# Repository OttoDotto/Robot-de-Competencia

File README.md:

# Proyecto Robot de Competencia

Este repositorio contiene el diseño y desarrollo de un **robot móvil autónomo** basado en **ESP32**, pensado para competencias de **seguidores de línea** y adaptable a otras categorías (sumo o fútbol robótico).

## 🏁 Objetivo
Este proyecto representa el **primer paso de la Facultad del Ejército Argentino en el mundo de la robótica competitiva**.  
Más allá del desarrollo técnico, nuestro propósito es:  
- Introducirnos en el ámbito de las competencias robóticas estudiantiles.  
- Presentar a nuestra institución en la comunidad tecnológica.  
- Generar experiencia para futuras participaciones en categorías como seguidor de línea, fútbol robótico y sumo.  
- Sentar las bases para que, en el futuro, la Facultad pueda convertirse en **sede de competencias de robótica**.  

## 🔧 Características principales
- **Microcontrolador**: ESP32 DevKit V1
- **Motores**: 2 × DC Pololu con controladores DRV8833 en configuración paralela
- **Sensores**: Array de 8 sensores reflectivos (QTR-8A)
- **Estructura**: Base y Diseño fabricado en impresión 3D
- **Conectividad**: Bluetooth, Wi-Fi y Control con mando PS
- **Aplicaciones**:  
  - Seguidor de línea (principal)  
  - Adaptación a fútbol robótico

## 📂 Contenido del repositorio
- `/Pcb Kicad` → esquemáticos y PCB en KiCad
- `/Fabricacion` → archivos para fabricacion casera del PCB
- `/Programacion` → códigos utilizados (Motores, Sensores, etc.)
- `/Documentos` → documentación, datasheets, imágenes de referencia del proyecto
- `/Galeria` → Fotografias, videos e imagenes del proyecto

## 📸 Galería (soon tm)

## 👥 Autores
Proyecto desarrollado en la **Facultad del Ejército Argentino** por el equipo **Legión de Ohm**.

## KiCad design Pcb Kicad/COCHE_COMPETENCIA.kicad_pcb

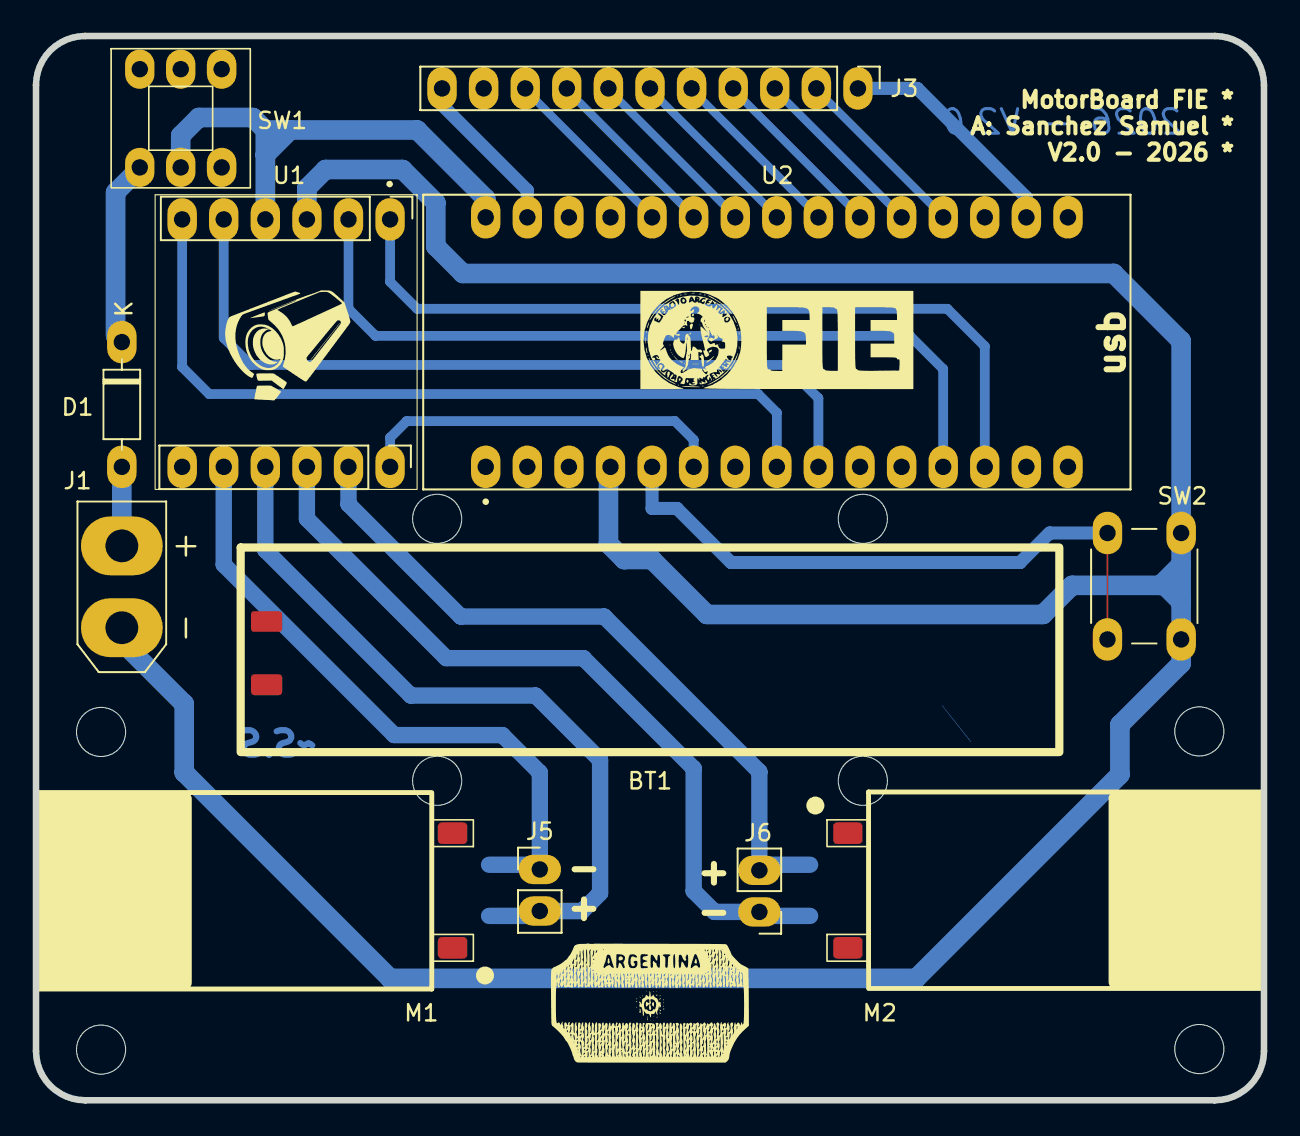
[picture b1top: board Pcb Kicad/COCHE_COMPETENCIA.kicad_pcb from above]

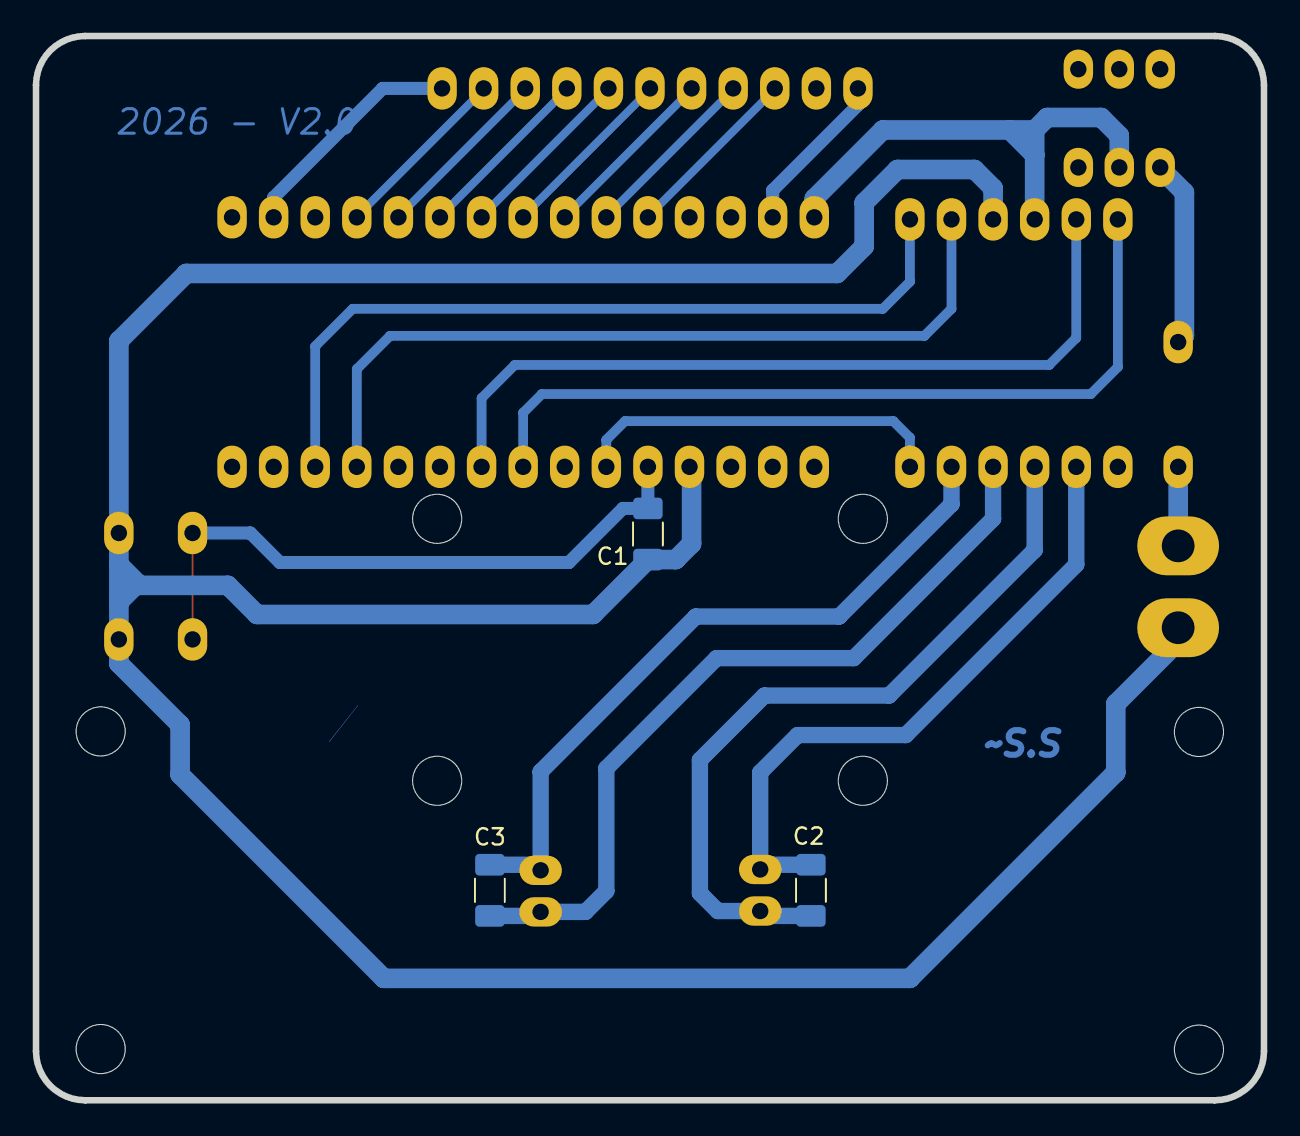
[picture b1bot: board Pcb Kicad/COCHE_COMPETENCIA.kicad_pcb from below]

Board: 2 copper layers, 75.0 x 65.0 mm, 15 parts (3 on the bottom side), 24 nets.

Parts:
BT1: 2S 70C 250mAH; Bateria_Lado
C1, C2, C3: 100n; C_1206_3216Metric_Pad1.33x1.80mm_HandSolder
D1: D_Schottky; D_DO-35_SOD27_P7.62mm_Horizontal
J1: BAT; AMASS_XT30UPB-M_1x02_P5.0mm_Vertical
J3: SENSORES; PinHeader_1x11_P2.54mm_Vertical
J5: M1; PinHeader_1x02_P2.54mm_Vertical
J6: M2; PinHeader_1x02_P2.54mm_Vertical
M1, M2: Pololu DC; pololu
SW1: ON/OFF; SWITCH_6PINS
SW2: SW_RUN; SW_PUSH_6mm_H5mm
U1: DRV8833
U2: ARDUINO_NANO; MODULE_ARDUINO_NANO

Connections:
+3.3V: J3.1, U2.17 (3V3)
/BAT+: D1.2 (A), J1.2
/IN_M1_A: U1.1 (IN4), U2.13 (D10)
/IN_M1_B: U1.2 (IN3), U2.12 (D9)
/IN_M2_A: U1.5 (IN2), U2.9 (D6)
/IN_M2_B: U1.6 (IN1), U2.8 (D5)
/OUT1+: C2.2, J5.2, U1.9 (OUT3)
/OUT1-: C2.1, J5.1, U1.8 (OUT4)
/OUT2+: C3.1, J6.2, U1.11 (OUT1)
/OUT2-: C3.2, J6.1, U1.10 (OUT2)
/S1: J3.9, U2.26 (A7)
/S2: J3.8, U2.25 (A6)
/S3: J3.7, U2.24 (A5)
/S4: J3.6, U2.23 (A4)
/S5: J3.5, U2.22 (A3)
/S6: J3.4, U2.21 (A2)
/S7: J3.3, U2.20 (A1)
/S8: J3.2, U2.19 (A0)
/SLEEP: U1.12 (SLEEP), U2.6 (D3)
/SW1: C1.1, SW2.1, U2.5 (D2)
GND: J3.11, U2.29 (GND_29)
GND_BAT: C1.2, J1.1, SW2.2, U1.3 (GND), U2.4 (GND_4)
unnamed: D1.1 (K), SW1.3 (B)
VCC: SW1.2 (C), U1.4 (VCC), U2.30 (VIN)

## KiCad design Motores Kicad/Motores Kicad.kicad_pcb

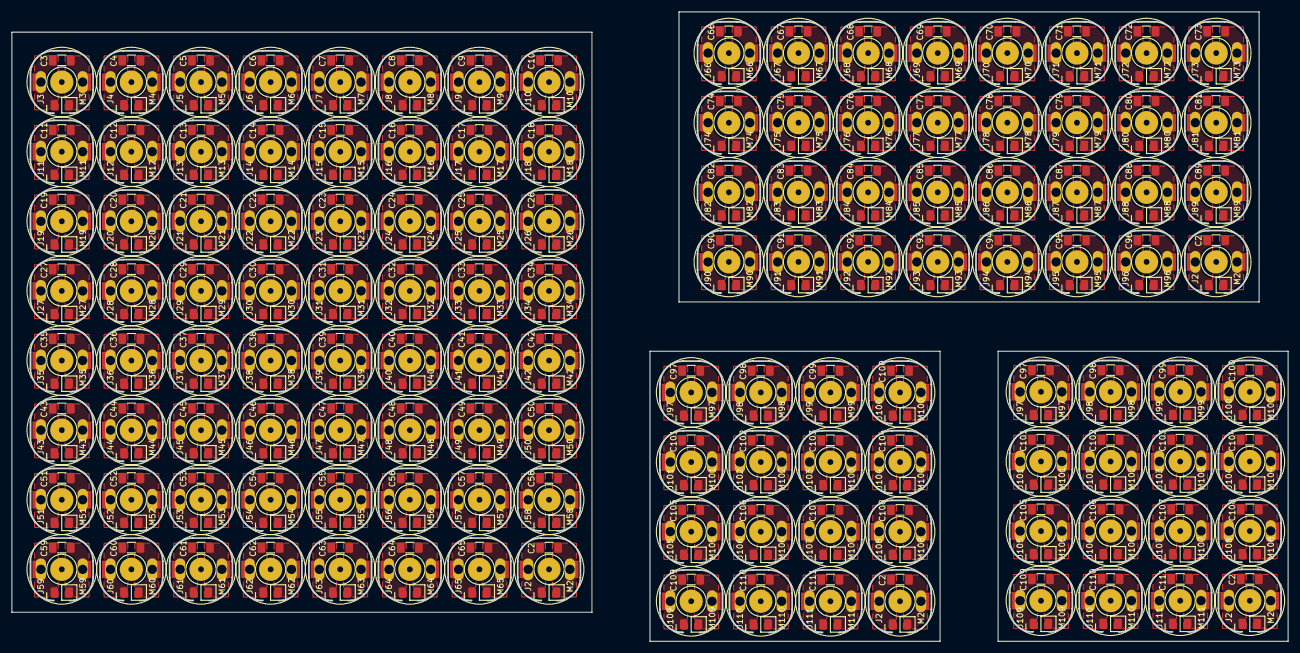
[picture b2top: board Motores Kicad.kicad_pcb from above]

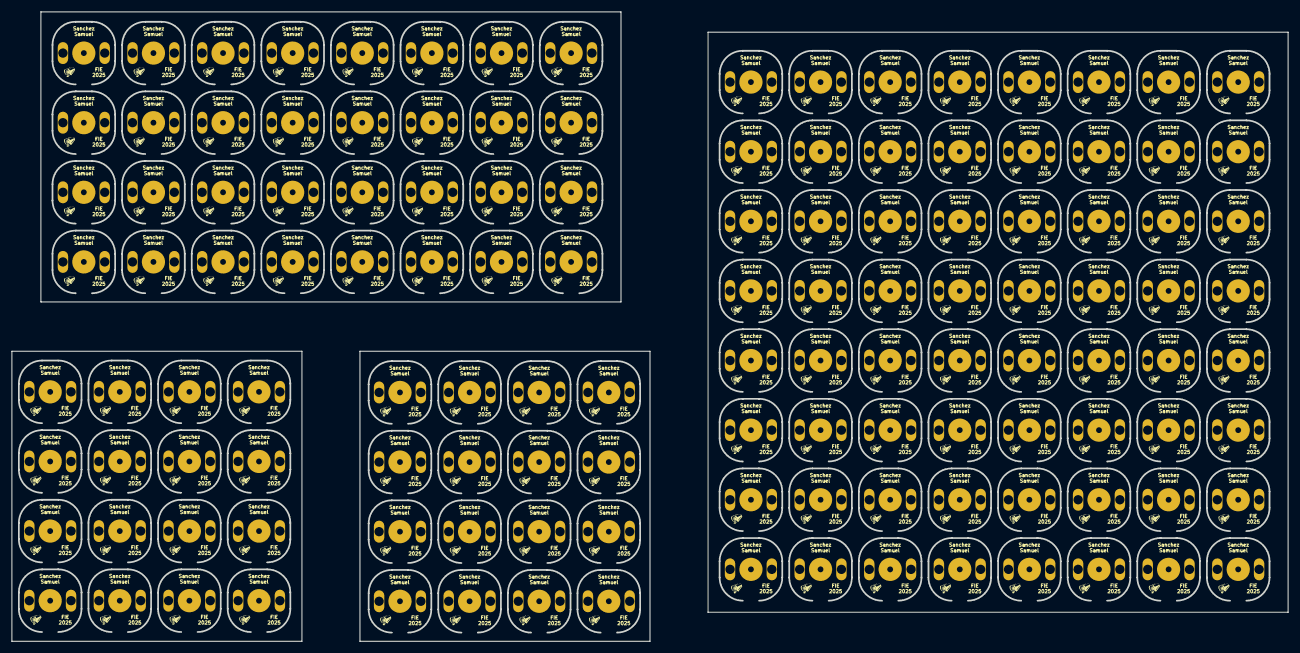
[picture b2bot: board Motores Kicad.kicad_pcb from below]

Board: 2 copper layers, 220.0 x 108.5 mm, 512 parts (128 on the bottom side), 2 nets, no tracks yet.

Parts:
C2, C2#2, C2#3, C2#4, C3, C4, C5, C6, C7, C8, C9, C10, C11, C12, C13, C14, C15, C16, C17, C18, C19, C20, C21, C22, C23, C24, C25, C26, C27, C28, C29, C30, C31, C32, C33, C34, C35, C36, C37, C38, C39, C40, C41, C42, C43, C44, C45, C46, C47, C48, C49, C50, C51, C52, C53, C54, C55, C56, C57, C58, C59, C60, C61, C62, C63, C64, C65, C66, C67, C68, C69, C70, C71, C72, C73, C74, C75, C76, C77, C78, C79, C80, C81, C82, C83, C84, C85, C86, C87, C88, C89, C90, C91, C92, C93, C94, C95, C96, C97, C97#2, C98, C98#2, C99, C99#2, C100, C100#2, C101, C101#2, C102, C102#2, C103, C103#2, C104, C104#2, C105, C105#2, C106, C106#2, C107, C107#2, C108, C108#2, C109, C109#2, C110, C110#2, C111, C111#2: 3.3nF; C_1206_3216Metric_Pad1.33x1.80mm_HandSolder
J2, J2#2, J2#3, J2#4, J3, J4, J5, J6, J7, J8, J9, J10, J11, J12, J13, J14, J15, J16, J17, J18, J19, J20, J21, J22, J23, J24, J25, J26, J27, J28, J29, J30, J31, J32, J33, J34, J35, J36, J37, J38, J39, J40, J41, J42, J43, J44, J45, J46, J47, J48, J49, J50, J51, J52, J53, J54, J55, J56, J57, J58, J59, J60, J61, J62, J63, J64, J65, J66, J67, J68, J69, J70, J71, J72, J73, J74, J75, J76, J77, J78, J79, J80, J81, J82, J83, J84, J85, J86, J87, J88, J89, J90, J91, J92, J93, J94, J95, J96, J97, J97#2, J98, J98#2, J99, J99#2, J100, J100#2, J101, J101#2, J102, J102#2, J103, J103#2, J104, J104#2, J105, J105#2, J106, J106#2, J107, J107#2, J108, J108#2, J109, J109#2, J110, J110#2, J111, J111#2: Vertical; PinHeader_1x02_P2.54mm_Vertical
M2, M2#2, M2#3, M2#4, M3, M4, M5, M6, M7, M8, M9, M10, M11, M12, M13, M14, M15, M16, M17, M18, M19, M20, M21, M22, M23, M24, M25, M26, M27, M28, M29, M30, M31, M32, M33, M34, M35, M36, M37, M38, M39, M40, M41, M42, M43, M44, M45, M46, M47, M48, M49, M50, M51, M52, M53, M54, M55, M56, M57, M58, M59, M60, M61, M62, M63, M64, M65, M66, M67, M68, M69, M70, M71, M72, M73, M74, M75, M76, M77, M78, M79, M80, M81, M82, M83, M84, M85, M86, M87, M88, M89, M90, M91, M92, M93, M94, M95, M96, M97, M97#2, M98, M98#2, M99, M99#2, M100, M100#2, M101, M101#2, M102, M102#2, M103, M103#2, M104, M104#2, M105, M105#2, M106, M106#2, M107, M107#2, M108, M108#2, M109, M109#2, M110, M110#2, M111, M111#2: Pololu
V4, V4#2, V4#3, V4#4, V5, V6, V7, V8, V9, V10, V11, V12, V13, V14, V15, V16, V17, V18, V19, V20, V21, V22, V23, V24, V25, V26, V27, V28, V29, V30, V31, V32, V33, V34, V35, V36, V37, V38, V39, V40, V41, V42, V43, V44, V45, V46, V47, V48, V49, V50, V51, V52, V53, V54, V55, V56, V57, V58, V59, V60, V61, V62, V63, V64, V65, V66, V67, V68, V69, V70, V71, V72, V73, V74, V75, V76, V77, V78, V79, V80, V81, V82, V83, V84, V85, V86, V87, V88, V89, V90, V91, V92, V93, V94, V95, V96, V97, V98, V99, V99#2, V100, V100#2, V101, V101#2, V102, V102#2, V103, V103#2, V104, V104#2, V105, V105#2, V106, V106#2, V107, V107#2, V108, V108#2, V109, V109#2, V110, V110#2, V111, V111#2, V112, V112#2, V113, V113#2: LOGO

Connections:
/(+): C2.1, C2#2.1, C2#3.1, C2#4.1, C3.1, C4.1, C5.1, C6.1, C7.1, C8.1, C9.1, C10.1, C11.1, C12.1, C13.1, C14.1, C15.1, C16.1, C17.1, C18.1, C19.1, C20.1, C21.1, C22.1, C23.1, C24.1, C25.1, C26.1, C27.1, C28.1, C29.1, C30.1, C31.1, C32.1, C33.1, C34.1, C35.1, C36.1, C37.1, C38.1, C39.1, C40.1, C41.1, C42.1, C43.1, C44.1, C45.1, C46.1, C47.1, C48.1, C49.1, C50.1, C51.1, C52.1, C53.1, C54.1, C55.1, C56.1, C57.1, C58.1, C59.1, C60.1, C61.1, C62.1, C63.1, C64.1, C65.1, C66.1, C67.1, C68.1, C69.1, C70.1, C71.1, C72.1, C73.1, C74.1, C75.1, C76.1, C77.1, C78.1, C79.1, C80.1, C81.1, C82.1, C83.1, C84.1, C85.1, C86.1, C87.1, C88.1, C89.1, C90.1, C91.1, C92.1, C93.1, C94.1, C95.1, C96.1, C97.1, C97#2.1, C98.1, C98#2.1, C99.1, C99#2.1, C100.1, C100#2.1, C101.1, C101#2.1, C102.1, C102#2.1, C103.1, C103#2.1, C104.1, C104#2.1, C105.1, C105#2.1, C106.1, C106#2.1, C107.1, C107#2.1, C108.1, C108#2.1, C109.1, C109#2.1, C110.1, C110#2.1, C111.1, C111#2.1, J2.1, J2#2.1, J2#3.1, J2#4.1, J3.1, J4.1, J5.1, J6.1, J7.1, J8.1, J9.1, J10.1, J11.1, J12.1, J13.1, J14.1, J15.1, J16.1, J17.1, J18.1, J19.1, J20.1, J21.1, J22.1, J23.1, J24.1, J25.1, J26.1, J27.1, J28.1, J29.1, J30.1, J31.1, J32.1, J33.1, J34.1, J35.1, J36.1, J37.1, J38.1, J39.1, J40.1, J41.1, J42.1, J43.1, J44.1, J45.1, J46.1, J47.1, J48.1, J49.1, J50.1, J51.1, J52.1, J53.1, J54.1, J55.1, J56.1, J57.1, J58.1, J59.1, J60.1, J61.1, J62.1, J63.1, J64.1, J65.1, J66.1, J67.1, J68.1, J69.1, J70.1, J71.1, J72.1, J73.1, J74.1, J75.1, J76.1, J77.1, J78.1, J79.1, J80.1, J81.1, J82.1, J83.1, J84.1, J85.1, J86.1, J87.1, J88.1, J89.1, J90.1, J91.1, J92.1, J93.1, J94.1, J95.1, J96.1, J97.1, J97#2.1, J98.1, J98#2.1, J99.1, J99#2.1, J100.1, J100#2.1, J101.1, J101#2.1, J102.1, J102#2.1, J103.1, J103#2.1, J104.1, J104#2.1, J105.1, J105#2.1, J106.1, J106#2.1, J107.1, J107#2.1, J108.1, J108#2.1, J109.1, J109#2.1, J110.1, J110#2.1, J111.1, J111#2.1, M2.1 (+), M2#2.1 (+), M2#3.1 (+), M2#4.1 (+), M3.1 (+), M4.1 (+), M5.1 (+), M6.1 (+), M7.1 (+), M8.1 (+), M9.1 (+), M10.1 (+), M11.1 (+), M12.1 (+), M13.1 (+), M14.1 (+), M15.1 (+), M16.1 (+), M17.1 (+), M18.1 (+), M19.1 (+), M20.1 (+), M21.1 (+), M22.1 (+), M23.1 (+), M24.1 (+), M25.1 (+), M26.1 (+), M27.1 (+), M28.1 (+), M29.1 (+), M30.1 (+), M31.1 (+), M32.1 (+), M33.1 (+), M34.1 (+), M35.1 (+), M36.1 (+), M37.1 (+), M38.1 (+), M39.1 (+), M40.1 (+), M41.1 (+), M42.1 (+), M43.1 (+)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
/(-): C2.2, C2#2.2, C2#3.2, C2#4.2, C3.2, C4.2, C5.2, C6.2, C7.2, C8.2, C9.2, C10.2, C11.2, C12.2, C13.2, C14.2, C15.2, C16.2, C17.2, C18.2, C19.2, C20.2, C21.2, C22.2, C23.2, C24.2, C25.2, C26.2, C27.2, C28.2, C29.2, C30.2, C31.2, C32.2, C33.2, C34.2, C35.2, C36.2, C37.2, C38.2, C39.2, C40.2, C41.2, C42.2, C43.2, C44.2, C45.2, C46.2, C47.2, C48.2, C49.2, C50.2, C51.2, C52.2, C53.2, C54.2, C55.2, C56.2, C57.2, C58.2, C59.2, C60.2, C61.2, C62.2, C63.2, C64.2, C65.2, C66.2, C67.2, C68.2, C69.2, C70.2, C71.2, C72.2, C73.2, C74.2, C75.2, C76.2, C77.2, C78.2, C79.2, C80.2, C81.2, C82.2, C83.2, C84.2, C85.2, C86.2, C87.2, C88.2, C89.2, C90.2, C91.2, C92.2, C93.2, C94.2, C95.2, C96.2, C97.2, C97#2.2, C98.2, C98#2.2, C99.2, C99#2.2, C100.2, C100#2.2, C101.2, C101#2.2, C102.2, C102#2.2, C103.2, C103#2.2, C104.2, C104#2.2, C105.2, C105#2.2, C106.2, C106#2.2, C107.2, C107#2.2, C108.2, C108#2.2, C109.2, C109#2.2, C110.2, C110#2.2, C111.2, C111#2.2, J2.2, J2#2.2, J2#3.2, J2#4.2, J3.2, J4.2, J5.2, J6.2, J7.2, J8.2, J9.2, J10.2, J11.2, J12.2, J13.2, J14.2, J15.2, J16.2, J17.2, J18.2, J19.2, J20.2, J21.2, J22.2, J23.2, J24.2, J25.2, J26.2, J27.2, J28.2, J29.2, J30.2, J31.2, J32.2, J33.2, J34.2, J35.2, J36.2, J37.2, J38.2, J39.2, J40.2, J41.2, J42.2, J43.2, J44.2, J45.2, J46.2, J47.2, J48.2, J49.2, J50.2, J51.2, J52.2, J53.2, J54.2, J55.2, J56.2, J57.2, J58.2, J59.2, J60.2, J61.2, J62.2, J63.2, J64.2, J65.2, J66.2, J67.2, J68.2, J69.2, J70.2, J71.2, J72.2, J73.2, J74.2, J75.2, J76.2, J77.2, J78.2, J79.2, J80.2, J81.2, J82.2, J83.2, J84.2, J85.2, J86.2, J87.2, J88.2, J89.2, J90.2, J91.2, J92.2, J93.2, J94.2, J95.2, J96.2, J97.2, J97#2.2, J98.2, J98#2.2, J99.2, J99#2.2, J100.2, J100#2.2, J101.2, J101#2.2, J102.2, J102#2.2, J103.2, J103#2.2, J104.2, J104#2.2, J105.2, J105#2.2, J106.2, J106#2.2, J107.2, J107#2.2, J108.2, J108#2.2, J109.2, J109#2.2, J110.2, J110#2.2, J111.2, J111#2.2, M2.2 (-), M2#2.2 (-), M2#3.2 (-), M2#4.2 (-), M3.2 (-), M4.2 (-), M5.2 (-), M6.2 (-), M7.2 (-), M8.2 (-), M9.2 (-), M10.2 (-), M11.2 (-), M12.2 (-), M13.2 (-), M14.2 (-), M15.2 (-), M16.2 (-), M17.2 (-), M18.2 (-), M19.2 (-), M20.2 (-), M21.2 (-), M22.2 (-), M23.2 (-), M24.2 (-), M25.2 (-), M26.2 (-), M27.2 (-), M28.2 (-), M29.2 (-), M30.2 (-), M31.2 (-), M32.2 (-), M33.2 (-), M34.2 (-), M35.2 (-), M36.2 (-), M37.2 (-), M38.2 (-), M39.2 (-), M40.2 (-), M41.2 (-), M42.2 (-), M43.2 (-)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

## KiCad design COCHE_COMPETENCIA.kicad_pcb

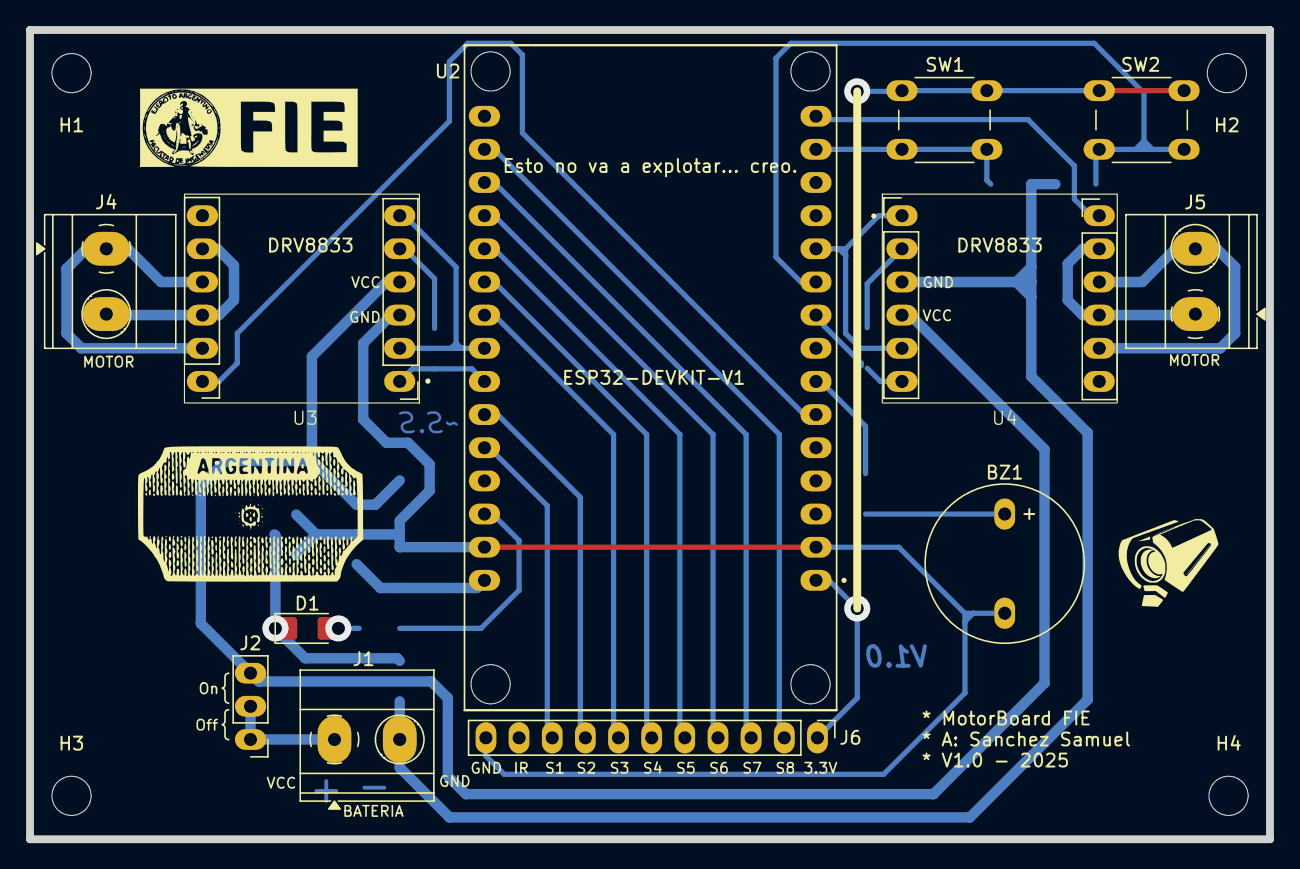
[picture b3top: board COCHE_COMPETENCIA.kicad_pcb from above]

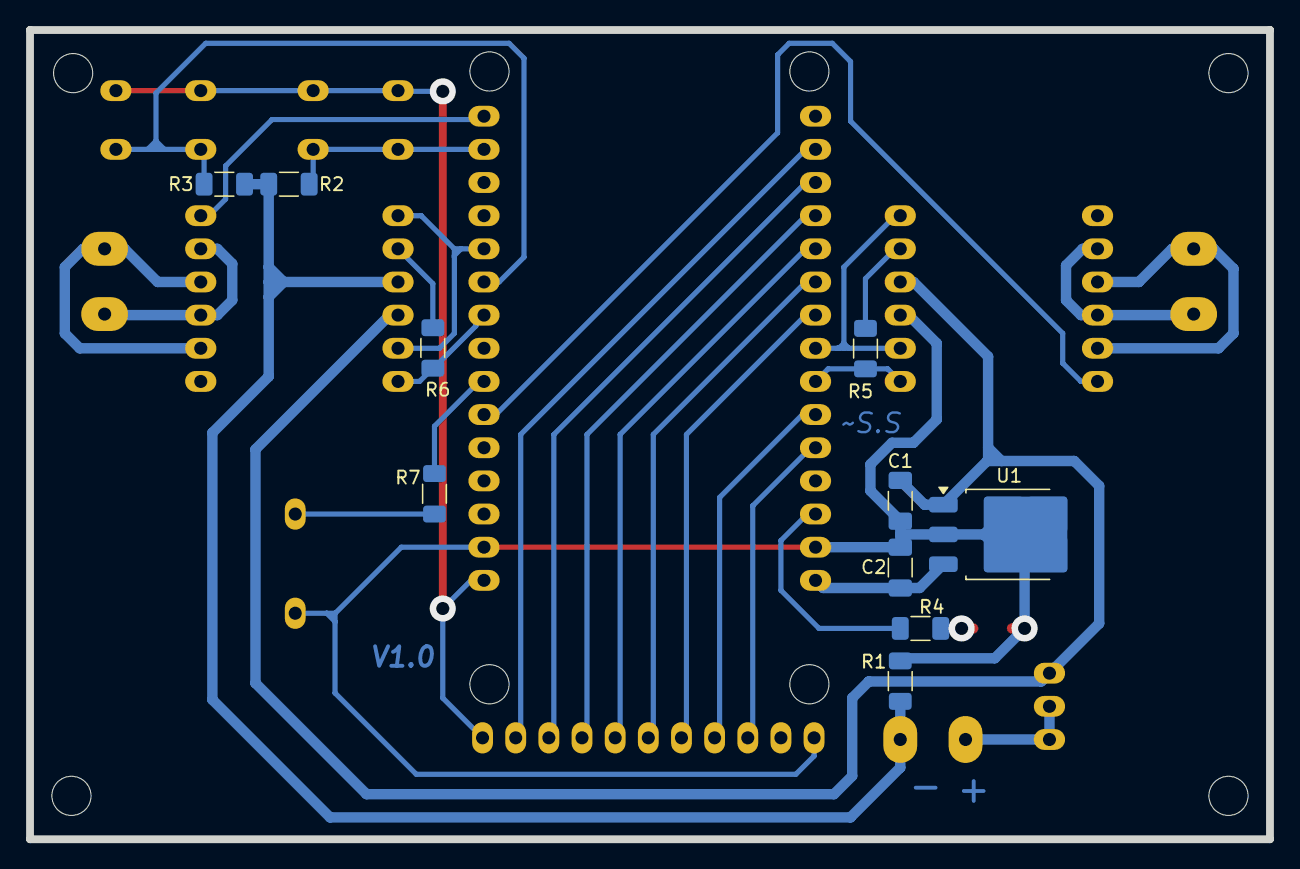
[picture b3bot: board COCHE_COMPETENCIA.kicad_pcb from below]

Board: 2 copper layers, 95.0 x 62.0 mm, 26 parts (10 on the bottom side), 31 nets.

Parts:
BZ1: Buzzer; MagneticBuzzer_ProSignal_ABI-009-RC
C1: 0.33u; C_1206_3216Metric_Pad1.33x1.80mm_HandSolder
C2: 0.1u; C_1206_3216Metric_Pad1.33x1.80mm_HandSolder
D1: LED_RED; LED_1206_3216Metric_Pad1.42x1.75mm_HandSolder
H1, H2, H3, H4: MountingHole; MountingHole_3mm
J1: BAT; TerminalBlock_Phoenix_MKDS-1,5-2_1x02_P5.00mm_Horizontal
J2: SWITCH; PinHeader_1x03_P2.54mm_Vertical
J4: M1; TerminalBlock_Phoenix_MKDS-1,5-2_1x02_P5.00mm_Horizontal
J5: M2; TerminalBlock_Phoenix_MKDS-1,5-2_1x02_P5.00mm_Horizontal
J6: SENSORES; PinHeader_1x11_P2.54mm_Vertical
R1, R5, R6, R7: 0; R_1206_3216Metric_Pad1.30x1.75mm_HandSolder
R2, R3: 10k; R_1206_3216Metric_Pad1.30x1.75mm_HandSolder
R4: 220; R_1206_3216Metric_Pad1.30x1.75mm_HandSolder
SW1, SW2: SW_Push; SW_PUSH_6mm_H5mm
U1: L7805; TO-252-3_TabPin2
U2: ESP32-DEVKIT-V1; MODULE_ESP32_DEVKIT_V1
U3, U4: DRV8833

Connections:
+3.3V: J6.1, SW1.1, SW2.1, U2.1 (3V3)
+5V: C2.1, U1.3 (OUT), U2.30 (VIN)
/BUZZER: R7.1, U2.7 (TX2)
/IN_M1_A: R5.1, U2.24 (D26), U3.1 (IN4)
/IN_M1_B: U2.23 (D25), U3.2 (IN3), U3.6 (IN1)
/IN_M2_A: U2.11 (D21), U4.1 (IN4), U4.5 (IN2)
/IN_M2_B: R6.1, U2.9 (D18), U4.6 (IN1)
/LED_LARGADA: R4.1, U2.28 (D13)
/S1: J6.9, U2.26 (D14)
/S2: J6.8, U2.25 (D27)
/S3: J6.7, U2.22 (D33)
/S4: J6.6, U2.21 (D32)
/S5: J6.5, U2.20 (D35)
/S6: J6.4, U2.19 (D34)
/S7: J6.3, U2.18 (VN)
/S8: J6.2, U2.17 (VP)
/SLEEP_M1: U2.6 (RX2), U3.12 (SLEEP)
/SLEEP_M2: U2.15 (D23), U4.12 (SLEEP)
/SW1: R2.1, SW1.2, U2.14 (D22)
/SW2: R3.1, SW2.2, U2.10 (D19)
GND: BZ1.2 (-), C1.2, C2.2, D1.1 (K), J1.2, J6.11, R1.1, R1.2, R2.2, R3.2, U1.2 (GND), U2.2 (GND), U2.29 (GND), U3.3 (GND), U4.3 (GND)
unnamed: BZ1.1 (+), R7.2
unnamed: D1.2 (A), R4.2
unnamed: J1.1, J2.1, J2.2
unnamed: J4.1, U3.9 (OUT3), U3.11 (OUT1)
unnamed: J4.2, U3.8 (OUT4), U3.10 (OUT2)
unnamed: J5.1, U4.9 (OUT3), U4.11 (OUT1)
unnamed: J5.2, U4.8 (OUT4), U4.10 (OUT2)
unnamed: R5.2, U3.5 (IN2)
unnamed: R6.2, U4.2 (IN3)
VCC: C1.1, J2.3, U1.1 (IN), U3.4 (VCC), U4.4 (VCC)

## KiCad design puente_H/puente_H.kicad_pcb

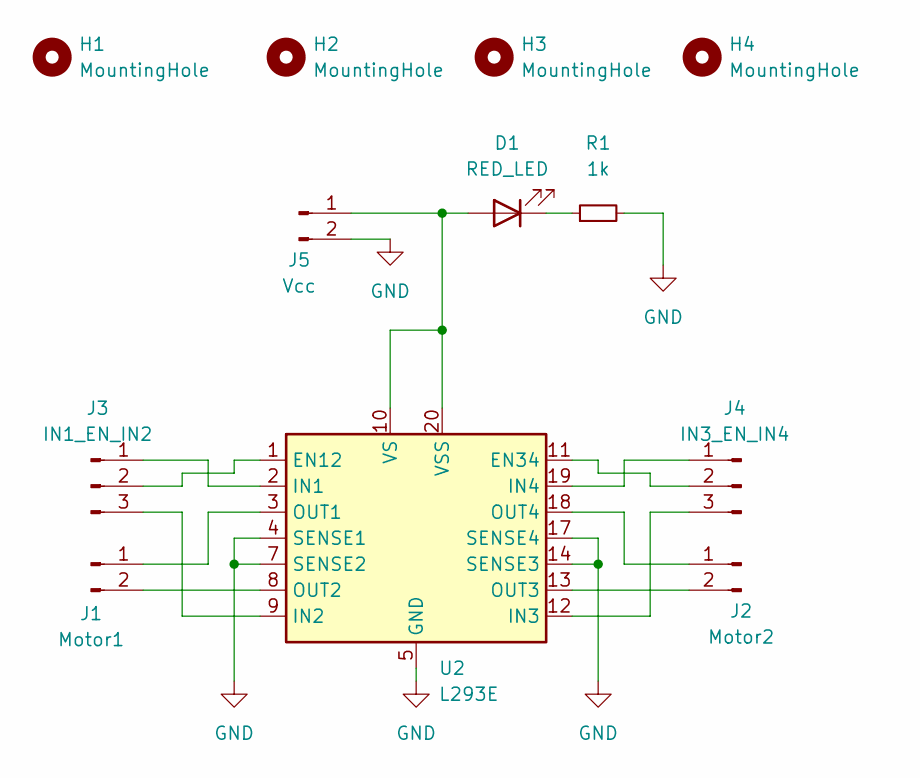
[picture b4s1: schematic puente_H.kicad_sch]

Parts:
D1: RED_LED; LED_1206_3216Metric_Pad1.42x1.75mm_HandSolder
H1, H2, H3, H4: MountingHole; MountingHole_2.1mm
J1: Motor1; PinHeader_1x02_P2.54mm_Vertical
J2: Motor2; PinHeader_1x02_P2.54mm_Vertical
J3: IN1_EN_IN2; PinHeader_1x03_P2.54mm_Vertical
J4: IN3_EN_IN4; PinHeader_1x03_P2.54mm_Vertical
J5: Vcc; PinHeader_1x02_P2.54mm_Vertical
R1: 1k; R_1206_3216Metric_Pad1.30x1.75mm_HandSolder
U2: L293E; DIP-20_W7.62mm_SMDSocket_SmallPads

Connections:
GND: J5.2, R1.2, U2.4 (SENSE1), U2.5 (GND), U2.6 (GND), U2.7 (SENSE2), U2.14 (SENSE3), U2.15 (GND), U2.16 (GND), U2.17 (SENSE4)
unnamed: D1.2 (A), J5.1, U2.10 (VS), U2.20 (VSS)
unnamed: D1.1 (K), R1.1
unnamed: J1.1, U2.3 (OUT1)
unnamed: J1.2, U2.8 (OUT2)
unnamed: J2.1, U2.18 (OUT4)
unnamed: J2.2, U2.13 (OUT3)
unnamed: J3.1, U2.2 (IN1)
unnamed: J3.2, U2.1 (EN12)
unnamed: J3.3, U2.9 (IN2)
unnamed: J4.1, U2.19 (IN4)
unnamed: J4.2, U2.11 (EN34)
unnamed: J4.3, U2.12 (IN3)

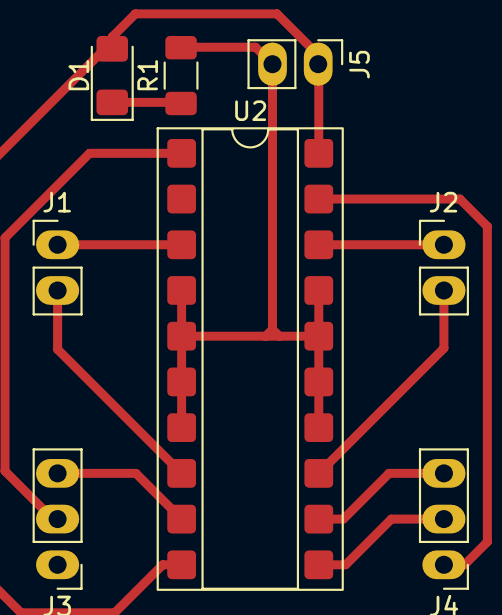
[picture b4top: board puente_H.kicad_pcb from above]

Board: 2 copper layers, 12 parts (0 on the bottom side), 13 nets.

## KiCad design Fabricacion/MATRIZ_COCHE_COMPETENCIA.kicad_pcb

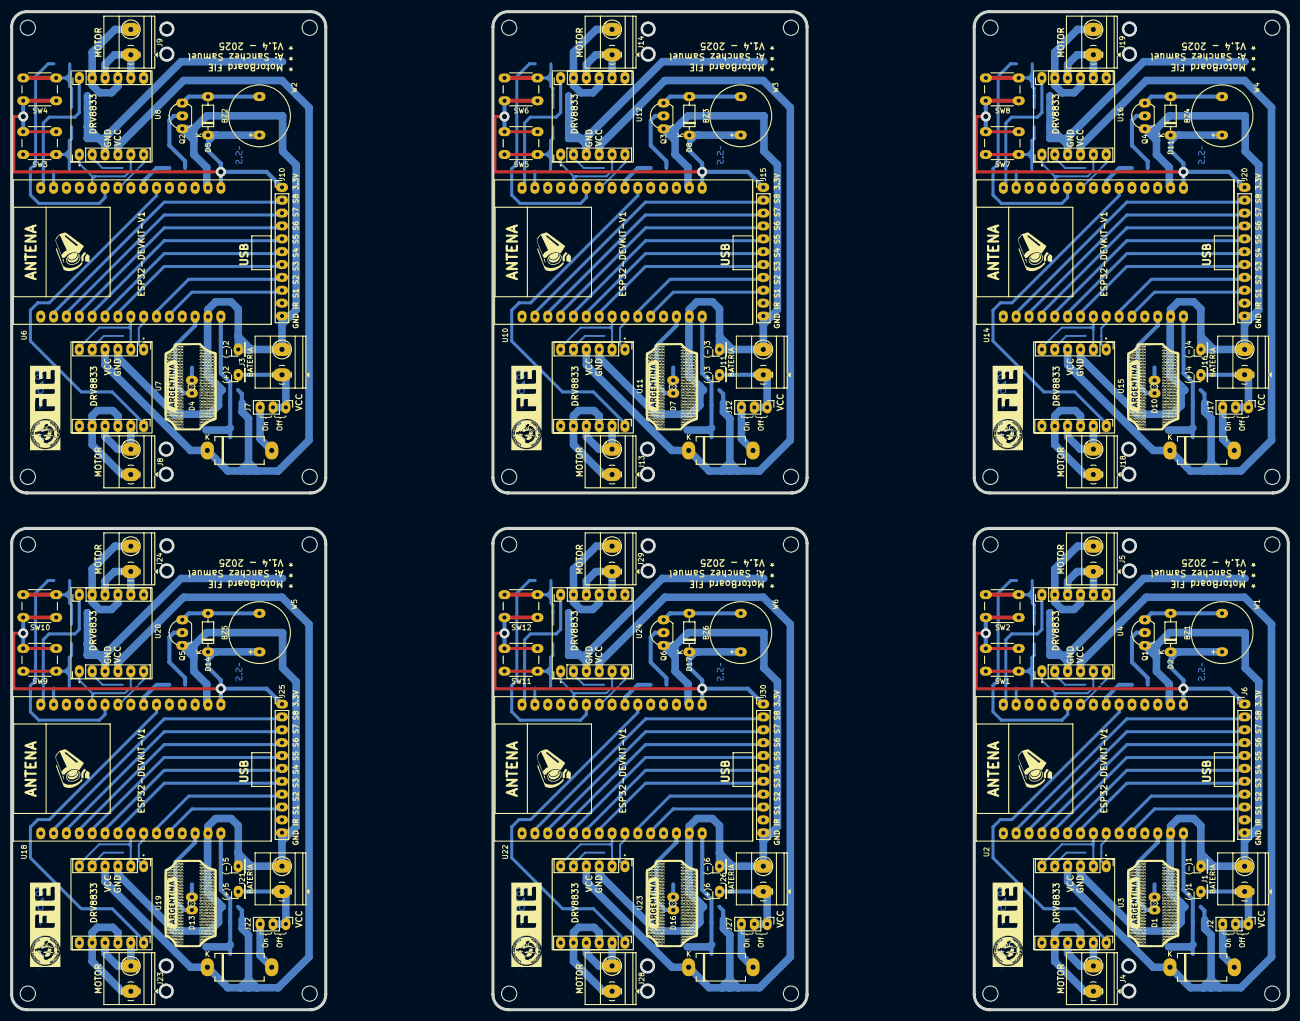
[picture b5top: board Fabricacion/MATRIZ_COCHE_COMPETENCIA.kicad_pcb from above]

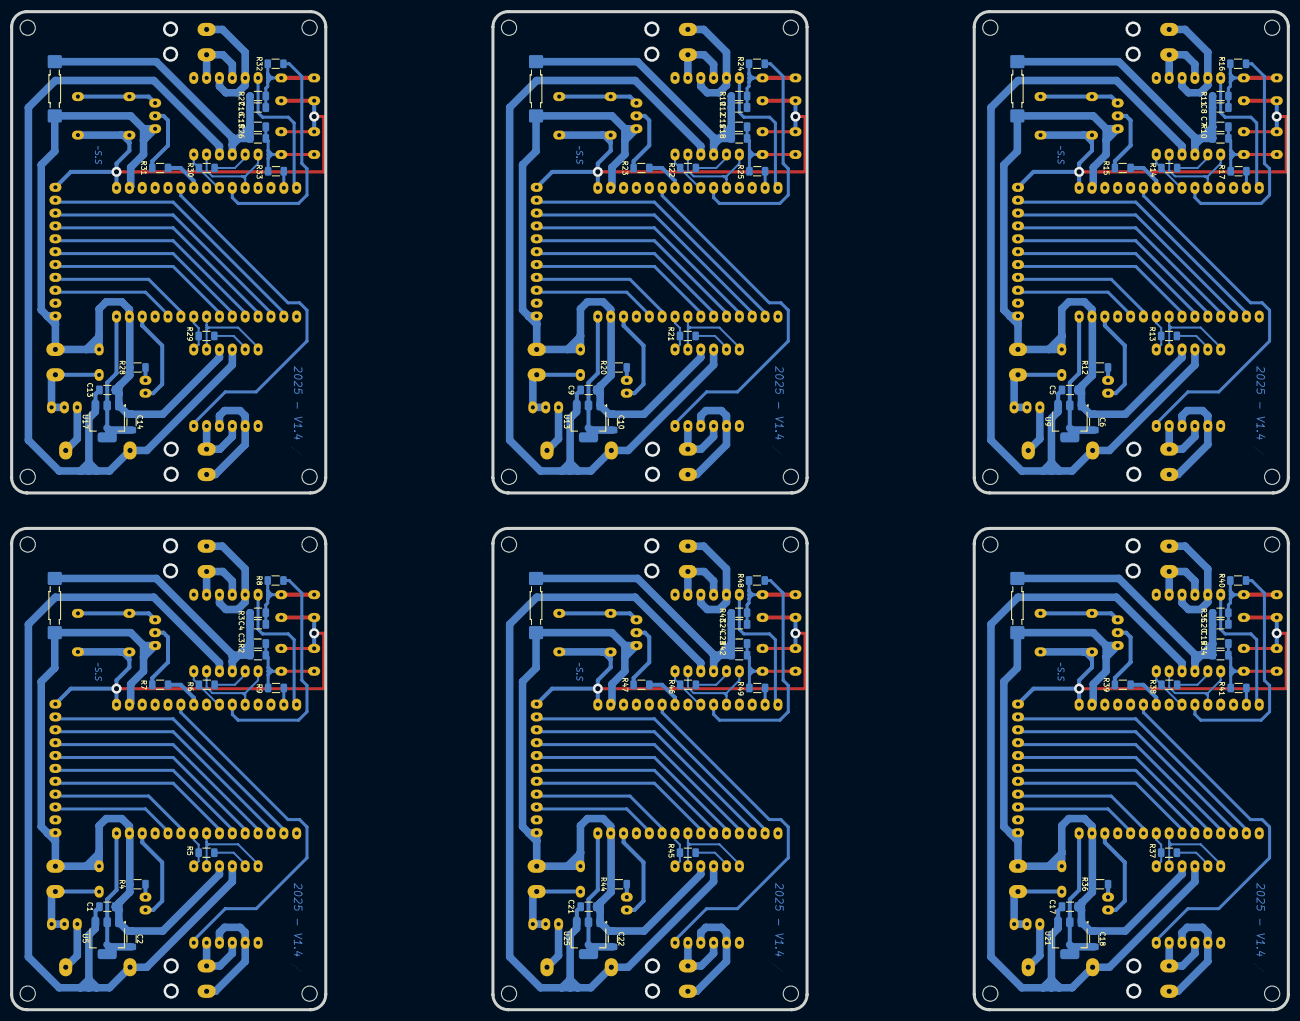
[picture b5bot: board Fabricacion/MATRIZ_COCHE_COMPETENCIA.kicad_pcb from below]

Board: 2 copper layers, 252.0 x 197.0 mm, 210 parts (84 on the bottom side), 35 nets.

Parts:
(+)1, (+)2, (+)3, (+)4, (+)5, (+)6: TestPoint; PinHeader_1x01_P2.54mm_Vertical
(-)1, (-)2, (-)3, (-)4, (-)5, (-)6: TestPoint; PinHeader_1x01_P2.54mm_Vertical
BZ1, BZ2, BZ3, BZ4, BZ5, BZ6: Buzzer; MagneticBuzzer_ProSignal_ABI-009-RC
C1, C3, C4, C5, C7, C8, C9, C11, C12, C13, C15, C16, C17, C19, C20, C21, C23, C24: 100n; C_1206_3216Metric_Pad1.33x1.80mm_HandSolder
C2, C6, C10, C14, C18, C22: 1u; C_1206_3216Metric_Pad1.33x1.80mm_HandSolder
D1, D4, D7, D10, D13, D16: LED_RED; LED_D5.0mm
D2, D5, D8, D11, D14, D17: 1N4148; D_DO-35_SOD27_P7.62mm_Horizontal
D3, D6, D9, D12, D15, D18: 1N5822; D_DO-201AD_P12.70mm_Horizontal
H1, H2, H3, H4, H5, H6, H7, H8, H9, H10, H11, H12, H13, H14, H15, H16, H17, H18, H19, H20, H21, H22, H23, H24: MountingHole; MountingHole_3mm
J1, J3, J11, J16, J21, J26: BAT; TerminalBlock_Phoenix_MKDS-1,5-2_1x02_P5.00mm_Horizontal
J2, J7, J12, J17, J22, J27: SWITCH; PinHeader_1x03_P2.54mm_Vertical
J4, J8, J13, J18, J23, J28: M1; TerminalBlock_Phoenix_MKDS-1,5-2_1x02_P5.00mm_Horizontal
J5, J9, J14, J19, J24, J29: M2; TerminalBlock_Phoenix_MKDS-1,5-2_1x02_P5.00mm_Horizontal
J6, J10, J15, J20, J25, J30: SENSORES; PinHeader_1x11_P2.54mm_Vertical
Q1, Q2, Q3, Q4, Q5, Q6: 2N3904; TO-92_Inline_Wide
R2, R3, R10, R11, R18, R19, R26, R27, R34, R35, R42, R43: 10k; R_1206_3216Metric_Pad1.30x1.75mm_HandSolder
R4, R12, R20, R28, R36, R44: 220; R_1206_3216Metric_Pad1.30x1.75mm_HandSolder
R5, R6, R13, R14, R21, R22, R29, R30, R37, R38, R45, R46: 0; R_1206_3216Metric_Pad1.30x1.75mm_HandSolder
R7, R15, R23, R31, R39, R47: 1k; R_1206_3216Metric_Pad1.30x1.75mm_HandSolder
R8, R9, R16, R17, R24, R25, R32, R33, R40, R41, R48, R49: 100; R_1206_3216Metric_Pad1.30x1.75mm_HandSolder
SW1, SW2, SW3, SW4, SW5, SW6, SW7, SW8, SW9, SW10, SW11, SW12: SW_Push; SW_PUSH_6mm_H5mm
U2, U6, U10, U14, U18, U22: ESP32-DEVKIT-V1; MODULE_ESP32_DEVKIT_V1
U3, U4, U7, U8, U11, U12, U15, U16, U19, U20, U23, U24: DRV8833
U5, U9, U13, U17, U21, U25: AMS1117; SOT-223-3_TabPin2
W1, W2, W3, W4, W5, W6: 5104; KEYSTONE_5104

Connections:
+3.3V: BZ1.1 (+), BZ2.1 (+), BZ3.1 (+), BZ4.1 (+), BZ5.1 (+), BZ6.1 (+), D2.1 (K), D5.1 (K), D8.1 (K), D11.1 (K), D14.1 (K), D17.1 (K), J6.1, J10.1, J15.1, J20.1, J25.1, J30.1, SW1.1, SW2.1, SW3.1, SW4.1, SW5.1, SW6.1, SW7.1, SW8.1, SW9.1, SW10.1, SW11.1, SW12.1, U2.1 (3V3), U6.1 (3V3), U10.1 (3V3), U14.1 (3V3), U18.1 (3V3), U22.1 (3V3)
+5V: C2.1, C6.1, C10.1, C14.1, C18.1, C22.1, U2.30 (VIN), U5.2 (VO), U6.30 (VIN), U9.2 (VO), U10.30 (VIN), U13.2 (VO), U14.30 (VIN), U17.2 (VO), U18.30 (VIN), U21.2 (VO), U22.30 (VIN), U25.2 (VO)
/BUZZER: R7.1, R15.1, R23.1, R31.1, R39.1, R47.1, U2.7 (TX2), U6.7 (TX2), U10.7 (TX2), U14.7 (TX2), U18.7 (TX2), U22.7 (TX2)
/IN_M1_A: R5.1, R13.1, R21.1, R29.1, R37.1, R45.1, U2.24 (D26), U3.1 (IN4), U6.24 (D26), U7.1 (IN4), U10.24 (D26), U11.1 (IN4), U14.24 (D26), U15.1 (IN4), U18.24 (D26), U19.1 (IN4), U22.24 (D26), U23.1 (IN4)
/IN_M1_B: U2.23 (D25), U3.2 (IN3), U3.6 (IN1), U6.23 (D25), U7.2 (IN3), U7.6 (IN1), U10.23 (D25), U11.2 (IN3), U11.6 (IN1), U14.23 (D25), U15.2 (IN3), U15.6 (IN1), U18.23 (D25), U19.2 (IN3), U19.6 (IN1), U22.23 (D25), U23.2 (IN3), U23.6 (IN1)
/IN_M2_A: U2.11 (D21), U4.1 (IN4), U4.5 (IN2), U6.11 (D21), U8.1 (IN4), U8.5 (IN2), U10.11 (D21), U12.1 (IN4), U12.5 (IN2), U14.11 (D21), U16.1 (IN4), U16.5 (IN2), U18.11 (D21), U20.1 (IN4), U20.5 (IN2), U22.11 (D21), U24.1 (IN4), U24.5 (IN2)
/IN_M2_B: R6.1, R14.1, R22.1, R30.1, R38.1, R46.1, U2.9 (D18), U4.6 (IN1), U6.9 (D18), U8.6 (IN1), U10.9 (D18), U12.6 (IN1), U14.9 (D18), U16.6 (IN1), U18.9 (D18), U20.6 (IN1), U22.9 (D18), U24.6 (IN1)
/LED_LARGADA: D1.2 (A), D4.2 (A), D7.2 (A), D10.2 (A), D13.2 (A), D16.2 (A), U2.28 (D13), U6.28 (D13), U10.28 (D13), U14.28 (D13), U18.28 (D13), U22.28 (D13)
/S1: J6.9, J10.9, J15.9, J20.9, J25.9, J30.9, U2.26 (D14), U6.26 (D14), U10.26 (D14), U14.26 (D14), U18.26 (D14), U22.26 (D14)
/S2: J6.8, J10.8, J15.8, J20.8, J25.8, J30.8, U2.25 (D27), U6.25 (D27), U10.25 (D27), U14.25 (D27), U18.25 (D27), U22.25 (D27)
/S3: J6.7, J10.7, J15.7, J20.7, J25.7, J30.7, U2.22 (D33), U6.22 (D33), U10.22 (D33), U14.22 (D33), U18.22 (D33), U22.22 (D33)
/S4: J6.6, J10.6, J15.6, J20.6, J25.6, J30.6, U2.21 (D32), U6.21 (D32), U10.21 (D32), U14.21 (D32), U18.21 (D32), U22.21 (D32)
/S5: J6.5, J10.5, J15.5, J20.5, J25.5, J30.5, U2.20 (D35), U6.20 (D35), U10.20 (D35), U14.20 (D35), U18.20 (D35), U22.20 (D35)
/S6: J6.4, J10.4, J15.4, J20.4, J25.4, J30.4, U2.19 (D34), U6.19 (D34), U10.19 (D34), U14.19 (D34), U18.19 (D34), U22.19 (D34)
/S7: J6.3, J10.3, J15.3, J20.3, J25.3, J30.3, U2.18 (VN), U6.18 (VN), U10.18 (VN), U14.18 (VN), U18.18 (VN), U22.18 (VN)
/S8: J6.2, J10.2, J15.2, J20.2, J25.2, J30.2, U2.17 (VP), U6.17 (VP), U10.17 (VP), U14.17 (VP), U18.17 (VP), U22.17 (VP)
/SLEEP_M1: U2.6 (RX2), U3.12 (SLEEP), U6.6 (RX2), U7.12 (SLEEP), U10.6 (RX2), U11.12 (SLEEP), U14.6 (RX2), U15.12 (SLEEP), U18.6 (RX2), U19.12 (SLEEP), U22.6 (RX2), U23.12 (SLEEP)
/SLEEP_M2: U2.15 (D23), U4.12 (SLEEP), U6.15 (D23), U8.12 (SLEEP), U10.15 (D23), U12.12 (SLEEP), U14.15 (D23), U16.12 (SLEEP), U18.15 (D23), U20.12 (SLEEP), U22.15 (D23), U24.12 (SLEEP)
/SW1: R9.2, R17.2, R25.2, R33.2, R41.2, R49.2, U2.14 (D22), U6.14 (D22), U10.14 (D22), U14.14 (D22), U18.14 (D22), U22.14 (D22)
/SW2: R8.2, R16.2, R24.2, R32.2, R40.2, R48.2, U2.10 (D19), U6.10 (D19), U10.10 (D19), U14.10 (D19), U18.10 (D19), U22.10 (D19)
GND: (-)1.1, (-)2.1, (-)3.1, (-)4.1, (-)5.1, (-)6.1, C1.2, C2.2, C3.2, C4.2, C5.2, C6.2, C7.2, C8.2, C9.2, C10.2, C11.2, C12.2, C13.2, C14.2, C15.2, C16.2, C17.2, C18.2, C19.2, C20.2, C21.2, C22.2, C23.2, C24.2, J1.2, J3.2, J6.11, J10.11, J11.2, J15.11, J16.2, J20.11, J21.2, J25.11, J26.2, J30.11, Q1.1 (E), Q2.1 (E), Q3.1 (E), Q4.1 (E), Q5.1 (E), Q6.1 (E), R2.2, R3.2, R4.2, R10.2, R11.2, R12.2, R18.2, R19.2, R20.2, R26.2, R27.2, R28.2, R34.2, R35.2, R36.2, R42.2, R43.2, R44.2, U2.2 (GND), U2.29 (GND), U3.3 (GND), U4.3 (GND), U5.1 (ADJ), U6.2 (GND), U6.29 (GND), U7.3 (GND), U8.3 (GND), U9.1 (ADJ), U10.2 (GND), U10.29 (GND), U11.3 (GND), U12.3 (GND), U13.1 (ADJ), U14.2 (GND), U14.29 (GND), U15.3 (GND), U16.3 (GND), U17.1 (ADJ), U18.2 (GND), U18.29 (GND), U19.3 (GND), U20.3 (GND), U21.1 (ADJ), U22.2 (GND), U22.29 (GND), U23.3 (GND), U24.3 (GND), U25.1 (ADJ), W1.1, W1.2, W2.1, W2.2, W3.1, W3.2, W4.1, W4.2, W5.1, W5.2, W6.1, W6.2
unnamed: BZ1.2 (-), BZ2.2 (-), BZ3.2 (-), BZ4.2 (-), BZ5.2 (-), BZ6.2 (-), D2.2 (A), D5.2 (A), D8.2 (A), D11.2 (A), D14.2 (A), D17.2 (A), Q1.3 (C), Q2.3 (C), Q3.3 (C), Q4.3 (C), Q5.3 (C), Q6.3 (C)
unnamed: C3.1, C7.1, C11.1, C15.1, C19.1, C23.1, R2.1, R9.1, R10.1, R17.1, R18.1, R25.1, R26.1, R33.1, R34.1, R41.1, R42.1, R49.1, SW1.2, SW3.2, SW5.2, SW7.2, SW9.2, SW11.2
unnamed: C4.1, C8.1, C12.1, C16.1, C20.1, C24.1, R3.1, R8.1, R11.1, R16.1, R19.1, R24.1, R27.1, R32.1, R35.1, R40.1, R43.1, R48.1, SW2.2, SW4.2, SW6.2, SW8.2, SW10.2, SW12.2
unnamed: D1.1 (K), D4.1 (K), D7.1 (K), D10.1 (K), D13.1 (K), D16.1 (K), R4.1, R12.1, R20.1, R28.1, R36.1, R44.1
unnamed: D3.2 (A), D6.2 (A), D9.2 (A), D12.2 (A), D15.2 (A), D18.2 (A), J2.3, J7.3, J12.3, J17.3, J22.3, J27.3
unnamed: (+)1.1, (+)2.1, (+)3.1, (+)4.1, (+)5.1, (+)6.1, J1.1, J2.1, J2.2, J3.1, J7.1, J7.2, J11.1, J12.1, J12.2, J16.1, J17.1, J17.2, J21.1, J22.1, J22.2, J26.1, J27.1, J27.2
unnamed: J4.1, J8.1, J13.1, J18.1, J23.1, J28.1, U3.8 (OUT4), U3.10 (OUT2), U7.8 (OUT4), U7.10 (OUT2), U11.8 (OUT4), U11.10 (OUT2), U15.8 (OUT4), U15.10 (OUT2), U19.8 (OUT4), U19.10 (OUT2), U23.8 (OUT4), U23.10 (OUT2)
unnamed: J4.2, J8.2, J13.2, J18.2, J23.2, J28.2, U3.9 (OUT3), U3.11 (OUT1), U7.9 (OUT3), U7.11 (OUT1), U11.9 (OUT3), U11.11 (OUT1), U15.9 (OUT3), U15.11 (OUT1), U19.9 (OUT3), U19.11 (OUT1), U23.9 (OUT3), U23.11 (OUT1)
unnamed: J5.1, J9.1, J14.1, J19.1, J24.1, J29.1, U4.8 (OUT4), U4.10 (OUT2), U8.8 (OUT4), U8.10 (OUT2), U12.8 (OUT4), U12.10 (OUT2), U16.8 (OUT4), U16.10 (OUT2), U20.8 (OUT4), U20.10 (OUT2), U24.8 (OUT4), U24.10 (OUT2)
unnamed: J5.2, J9.2, J14.2, J19.2, J24.2, J29.2, U4.9 (OUT3), U4.11 (OUT1), U8.9 (OUT3), U8.11 (OUT1), U12.9 (OUT3), U12.11 (OUT1), U16.9 (OUT3), U16.11 (OUT1), U20.9 (OUT3), U20.11 (OUT1), U24.9 (OUT3), U24.11 (OUT1)
unnamed: Q1.2 (B), Q2.2 (B), Q3.2 (B), Q4.2 (B), Q5.2 (B), Q6.2 (B), R7.2, R15.2, R23.2, R31.2, R39.2, R47.2
unnamed: R5.2, R13.2, R21.2, R29.2, R37.2, R45.2, U3.5 (IN2), U7.5 (IN2), U11.5 (IN2), U15.5 (IN2), U19.5 (IN2), U23.5 (IN2)
unnamed: R6.2, R14.2, R22.2, R30.2, R38.2, R46.2, U4.2 (IN3), U8.2 (IN3), U12.2 (IN3), U16.2 (IN3), U20.2 (IN3), U24.2 (IN3)
VCC: C1.1, C5.1, C9.1, C13.1, C17.1, C21.1, D3.1 (K), D6.1 (K), D9.1 (K), D12.1 (K), D15.1 (K), D18.1 (K), U3.4 (VCC), U4.4 (VCC), U5.3 (VI), U7.4 (VCC), U8.4 (VCC), U9.3 (VI), U11.4 (VCC), U12.4 (VCC), U13.3 (VI), U15.4 (VCC), U16.4 (VCC), U17.3 (VI), U19.4 (VCC), U20.4 (VCC), U21.3 (VI), U23.4 (VCC), U24.4 (VCC), U25.3 (VI)
